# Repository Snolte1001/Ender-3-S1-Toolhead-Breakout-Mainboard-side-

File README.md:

# Ender-3-S1-Toolhead-Breakout-Mainboard-side-
Ender 3 S1 Toolhead Breakout (Mainboard side)

Breakout PCB for Ender 3 S1 toolhead cable mainboard side.  
Allows the use of another mainboard without having to change the original cable.

NOTE !
Due to the circuit in the toolhead, it is only possible to use 24V fan, because fan + and heat cartridge share the same wire ! 

All connectors JST-XH series.  
Pin header for flat ribbon cable TRU COMPONENTS 1589712 or compatible with 2mm pitch and 30 pin

The .zip file is ready to be uploaded to your trusted PCB manufacturer. PCP Way and Aisler are tested.

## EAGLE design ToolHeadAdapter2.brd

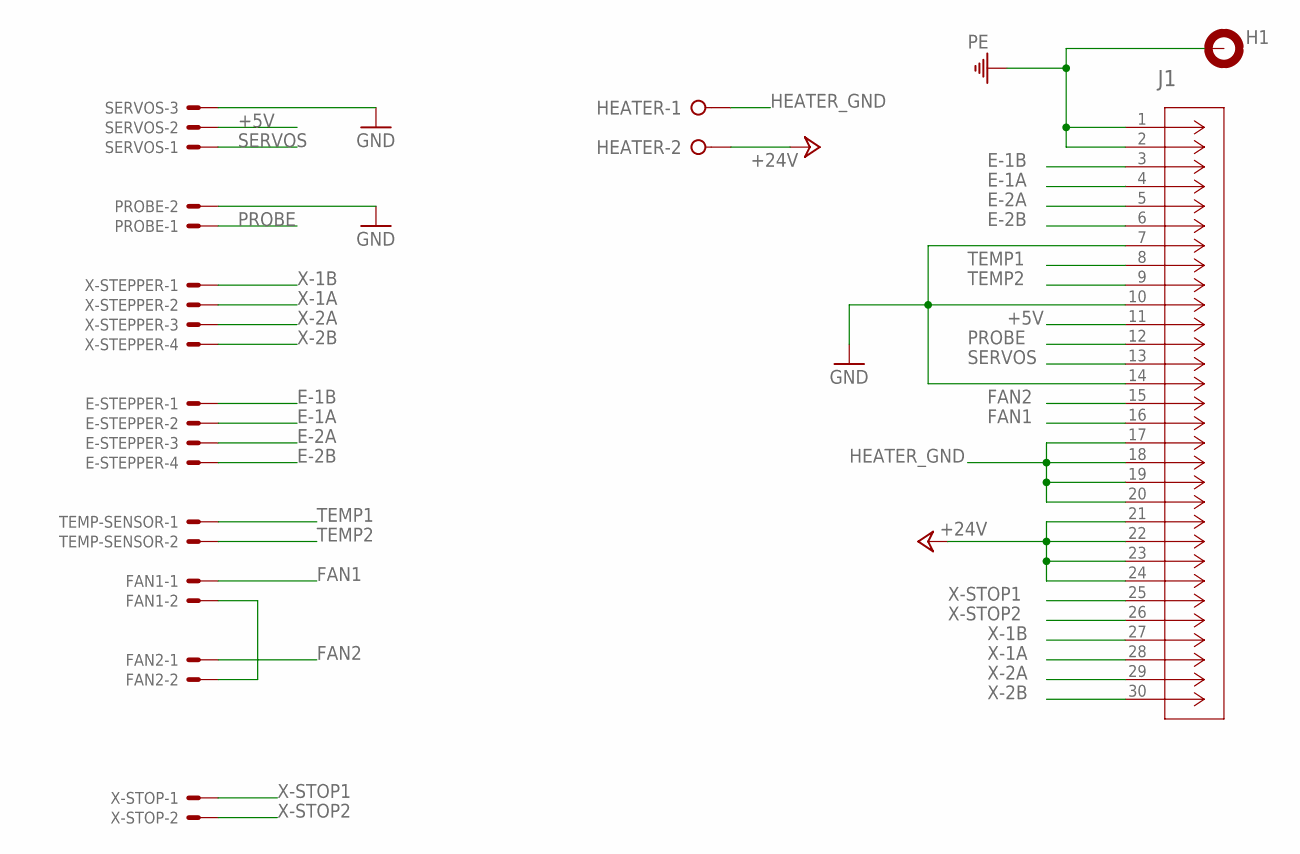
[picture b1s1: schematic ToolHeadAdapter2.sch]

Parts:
E-STEPPER: JST-XH-04-PIN-LONG-PAD; JST-XH-04-PACKAGE-LONG-PAD
FAN1, FAN2: JST-XH-02-PIN-LONG-PAD; JST-XH-02-PACKAGE-LONG-PAD
H1: MOUNT-PAD-ROUND3.2; 3,2-PAD
HEATER: W237-02P; W237-132
J1: EHT-115-01-S-D; CONN30_15-01-F-D_SAI
PROBE: JST-XH-02-PIN-LONG-PAD; JST-XH-02-PACKAGE-LONG-PAD
SERVOS: JST-XH-03-PIN-LONG-PAD; JST-XH-03-PACKAGE-LONG-PAD
TEMP-SENSOR: JST-XH-02-PIN-LONG-PAD; JST-XH-02-PACKAGE-LONG-PAD
X-STEPPER: JST-XH-04-PIN-LONG-PAD; JST-XH-04-PACKAGE-LONG-PAD
X-STOP: JST-XH-02-PIN-LONG-PAD; JST-XH-02-PACKAGE-LONG-PAD

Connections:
+5V: J1.11, SERVOS.2
+24V: HEATER.2, J1.21, J1.22, J1.23, J1.24
E-1A: E-STEPPER.2, J1.4
E-1B: E-STEPPER.1, J1.3
E-2A: E-STEPPER.3, J1.5
E-2B: E-STEPPER.4, J1.6
FAN1: FAN1.1, J1.16
FAN2: FAN2.1, J1.15
GND: J1.7, J1.10, J1.14, PROBE.2, SERVOS.3
HEATER_GND: HEATER.1, J1.17, J1.18, J1.19, J1.20
unnamed: FAN1.2, FAN2.2
PE: H1.B3,2, J1.1, J1.2
PROBE: J1.12, PROBE.1
SERVOS: J1.13, SERVOS.1
TEMP1: J1.8, TEMP-SENSOR.1
TEMP2: J1.9, TEMP-SENSOR.2
X-1A: J1.28, X-STEPPER.2
X-1B: J1.27, X-STEPPER.1
X-2A: J1.29, X-STEPPER.3
X-2B: J1.30, X-STEPPER.4
X-STOP1: J1.25, X-STOP.1
X-STOP2: J1.26, X-STOP.2

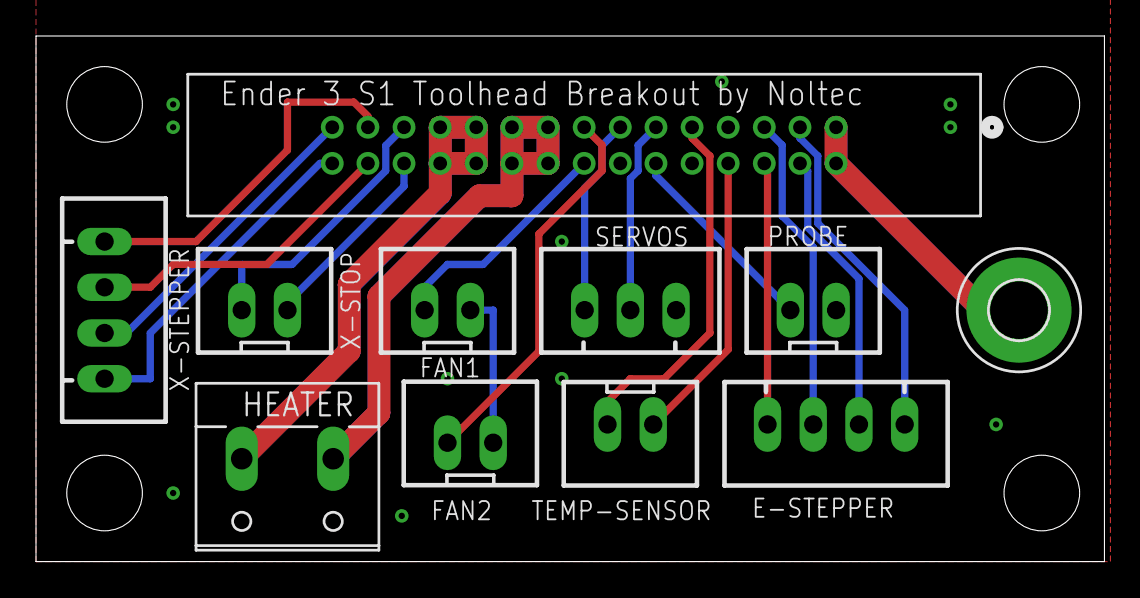
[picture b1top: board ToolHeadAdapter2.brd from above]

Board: 2 copper layers, 59.4 x 29.2 mm, 11 parts (0 on the bottom side), 22 nets.

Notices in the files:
parts and their libraries:
COPYRIGHT: Copyright (C) 2022 Ultra Librarian. All rights reserved.
